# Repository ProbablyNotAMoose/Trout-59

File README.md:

# Trout-59
Trout 59 key pcb - UT47.2 layout + southpaw numpad

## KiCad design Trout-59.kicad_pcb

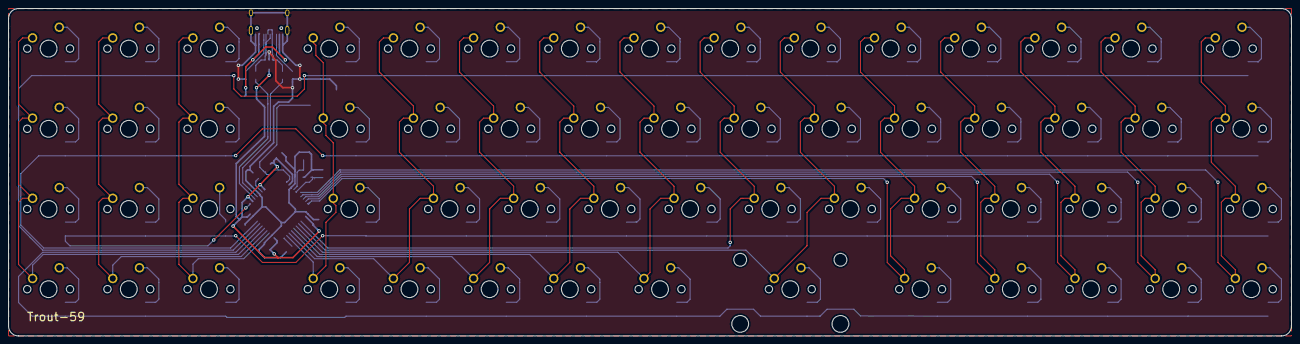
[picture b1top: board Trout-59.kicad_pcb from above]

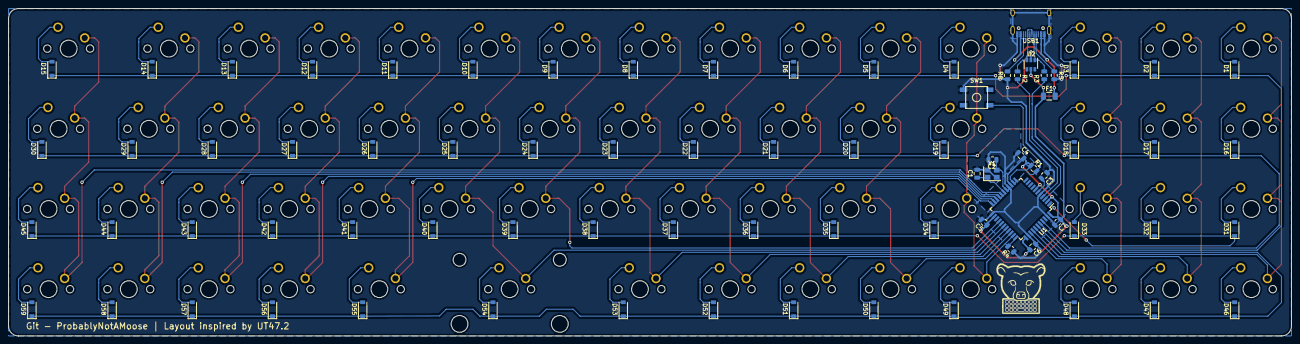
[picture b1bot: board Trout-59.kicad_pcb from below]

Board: 2 copper layers, 304.8 x 77.8 mm, 137 parts (78 on the bottom side), 92 nets.

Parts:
C1, C2: 22pF; C_0805_2012Metric
C3: 1uF; C_0805_2012Metric
C4, C5, C6: 0.1uF; C_0805_2012Metric
C7: 10uF; C_0805_2012Metric
D1, D2, D3, D4, D5, D6, D7, D8, D9, D10, D11, D12, D13, D14, D15, D16, D17, D18, D19, D20, D21, D22, D23, D24, D25, D26, D27, D28, D29, D30, D31, D32, D33, D34, D35, D36, D37, D38, D39, D40, D41, D42, D43, D44, D45, D46, D47, D48, D49, D50, D51, D52, D53, D54, D55, D56, D57, D58, D59: SOD-123; D_SOD-123
F1: 500mA; Fuse_1206_3216Metric
MX1, MX2, MX3, MX4, MX5, MX6, MX7, MX8, MX9, MX10, MX11, MX12, MX13, MX14, MX16, MX17, MX18, MX20, MX21, MX22, MX23, MX24, MX25, MX26, MX27, MX28, MX29, MX31, MX32, MX33, MX35, MX36, MX37, MX38, MX39, MX40, MX41, MX42, MX43, MX44, MX45, MX46, MX47, MX48, MX49, MX50, MX51, MX52, MX56, MX57, MX58, MX59: MX-NoLED; MXOnly-1U-NoLED
MX15, MX34: MX-NoLED; MXOnly-1.5U-NoLED
MX19, MX30, MX53, MX55: MX-NoLED; MXOnly-1.25U-NoLED
MX54: MX-NoLED; MXOnly-2U-NoLED
R1, R4: 10k; R_0805_2012Metric
R2, R3: 22; R_0805_2012Metric
R5, R6: 5.1k; R_0805_2012Metric
SW1: SW_Push; SKQG-1155865
U1: ATmega32U4-AU; TQFP-44_10x10mm_P0.8mm
U2: SRV05-4; SOT-23-6
USB1: HRO-TYPE-C-31-M-12
Y1: 16MHz; Crystal_SMD_3225-4Pin_3.2x2.5mm

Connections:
+5V: C4.1, C5.1, C6.1, C7.1, F1.1, R1.1, U1.2, U1.7, U1.14, U1.24, U1.34, U1.44, U2.5
Col0: MX1.1, MX16.1, MX31.1, MX46.1, U1.38
Col1: MX2.1, MX17.1, MX32.1, MX47.1, U1.37
Col2: MX3.1, MX18.1, MX33.1, MX48.1, U1.36
Col3: MX4.1, MX19.1, MX34.1, MX49.1, U1.32
Col4: MX5.1, MX20.1, MX35.1, MX50.1, U1.31
Col5: MX6.1, MX21.1, MX36.1, MX51.1, U1.30
Col6: MX7.1, MX22.1, MX37.1, MX52.1, U1.29
Col7: MX8.1, MX23.1, MX38.1, MX53.1, U1.28
Col8: MX9.1, MX24.1, MX39.1, U1.26
Col9: MX10.1, MX25.1, MX40.1, MX54.1, U1.27
Col10: MX11.1, MX26.1, MX41.1, MX55.1, U1.22
Col11: MX12.1, MX27.1, MX42.1, MX56.1, U1.21
Col12: MX13.1, MX28.1, MX43.1, MX57.1, U1.20
Col13: MX14.1, MX29.1, MX44.1, MX58.1, U1.19
Col14: MX15.1, MX30.1, MX45.1, MX59.1, U1.18
D+: R2.2, U2.3, USB1.6, USB1.8
D-: R3.2, U2.1, USB1.5, USB1.7
GND: C1.1, C2.1, C3.2, C4.2, C5.2, C6.2, C7.2, R4.1, R5.1, R6.1, SW1.1, U1.5, U1.15, U1.23, U1.35, U1.43, U2.2, USB1.1, USB1.12, USB1.13, Y1.2, Y1.4
unnamed: C1.2, U1.17, Y1.1
unnamed: C2.2, U1.16, Y1.3
unnamed: C3.1, U1.6
unnamed: D1.2, MX1.2
unnamed: D2.2, MX2.2
unnamed: D3.2, MX3.2
unnamed: D4.2, MX4.2
unnamed: D5.2, MX5.2
unnamed: D6.2, MX6.2
unnamed: D7.2, MX7.2
unnamed: D8.2, MX8.2
unnamed: D9.2, MX9.2
unnamed: D10.2, MX10.2
unnamed: D11.2, MX11.2
unnamed: D12.2, MX12.2
unnamed: D13.2, MX13.2
unnamed: D14.2, MX14.2
unnamed: D15.2, MX15.2
unnamed: D16.2, MX16.2
unnamed: D17.2, MX17.2
unnamed: D18.2, MX18.2
unnamed: D19.2, MX19.2
unnamed: D20.2, MX20.2
unnamed: D21.2, MX21.2
unnamed: D22.2, MX22.2
unnamed: D23.2, MX23.2
unnamed: D24.2, MX24.2
unnamed: D25.2, MX25.2
unnamed: D26.2, MX26.2
unnamed: D27.2, MX27.2
unnamed: D28.2, MX28.2
unnamed: D29.2, MX29.2
unnamed: D30.2, MX30.2
unnamed: D31.2, MX31.2
unnamed: D32.2, MX32.2
unnamed: D33.2, MX33.2
unnamed: D34.2, MX34.2
unnamed: D35.2, MX35.2
unnamed: D36.2, MX36.2
unnamed: D37.2, MX37.2
unnamed: D38.2, MX38.2
unnamed: D39.2, MX39.2
unnamed: D40.2, MX40.2
unnamed: D41.2, MX41.2
unnamed: D42.2, MX42.2
unnamed: D43.2, MX43.2
unnamed: D44.2, MX44.2
unnamed: D45.2, MX45.2
unnamed: D46.2, MX46.2
unnamed: D47.2, MX47.2
unnamed: D48.2, MX48.2
unnamed: D49.2, MX49.2
unnamed: D50.2, MX50.2
unnamed: D51.2, MX51.2
unnamed: D52.2, MX52.2
unnamed: D53.2, MX53.2
unnamed: D54.2, MX54.2
unnamed: D55.2, MX55.2
unnamed: D56.2, MX56.2
unnamed: D57.2, MX57.2
unnamed: D58.2, MX58.2
unnamed: D59.2, MX59.2
unnamed: R1.2, SW1.2, U1.13
unnamed: R2.1, U1.4
unnamed: R3.1, U1.3
unnamed: R4.2, U1.33
unnamed: R5.2, USB1.4
unnamed: R6.2, USB1.10
Row0: D1.1, D2.1, D3.1, D4.1, D5.1, D6.1, D7.1, D8.1, D9.1, D10.1, D11.1, D12.1, D13.1, D14.1, D15.1, U1.40
Row1: D16.1, D17.1, D18.1, D19.1, D20.1, D21.1, D22.1, D23.1, D24.1, D25.1, D26.1, D27.1, D28.1, D29.1, D30.1, U1.41
Row2: D31.1, D32.1, D33.1, D34.1, D35.1, D36.1, D37.1, D38.1, D39.1, D40.1, D41.1, D42.1, D43.1, D44.1, D45.1, U1.1
Row3: D46.1, D47.1, D48.1, D49.1, D50.1, D51.1, D52.1, D53.1, D54.1, D55.1, D56.1, D57.1, D58.1, D59.1, U1.39
VCC: F1.2, USB1.2, USB1.11

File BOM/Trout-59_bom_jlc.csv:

Comment,Designator,Footprint,LCSC Part #
22pF,"C1,C2",C_0805_2012Metric,C1804
1uF,C3,C_0805_2012Metric,C28323
0.1uF,"C4,C5,C6",C_0805_2012Metric,C49678
10uF,C7,C_0805_2012Metric,C15850
SOD-123,"D1,D3,D4,D5,D6,D7,D8,D9,D10,D11,D12,D13,D14,D15,D16,D17,D18,D19,D20,D21,D22,D23,D24,D25,D26,D27,D28,D29,D30,D31,D32,D33,D34,D35,D36,D37,D38,D39,D40,D41,D42,D43,D44,D45,D46,D47,D48,D49,D50,D51,D52,D53,D54,D55,D56,D57,D58,D59,D2",D_SOD-123,C8598
500mA,F1,Fuse_1206_3216Metric,C151162
22,"R2,R3",R_0805_2012Metric,C17520
10k,"R4,R1",R_0805_2012Metric,C17414
5.1k,"R6,R5",R_0805_2012Metric,C27834
16MHz,Y1,Crystal_SMD_3225-4Pin_3.2x2.5mm,C13738
ATmega32U4-AU,U1,TQFP-44_10x10mm_P0.8mm,C44854
SRV05-4,U2,SOT-23-6,C85364

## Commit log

2020-06-28 Initial Publication
2020-06-29 Gerber files updated
2020-06-30 Multiple changes to USB/crystal routingv
    Crystal ground plane defined, C2 and crystal location updated, row 0 rerouted, and Fuse rotated
2020-06-30 Ground planes updated
2020-07-01 Finalization
    Crystal ground plane separated from main groung, gerber and BOM files finalized
